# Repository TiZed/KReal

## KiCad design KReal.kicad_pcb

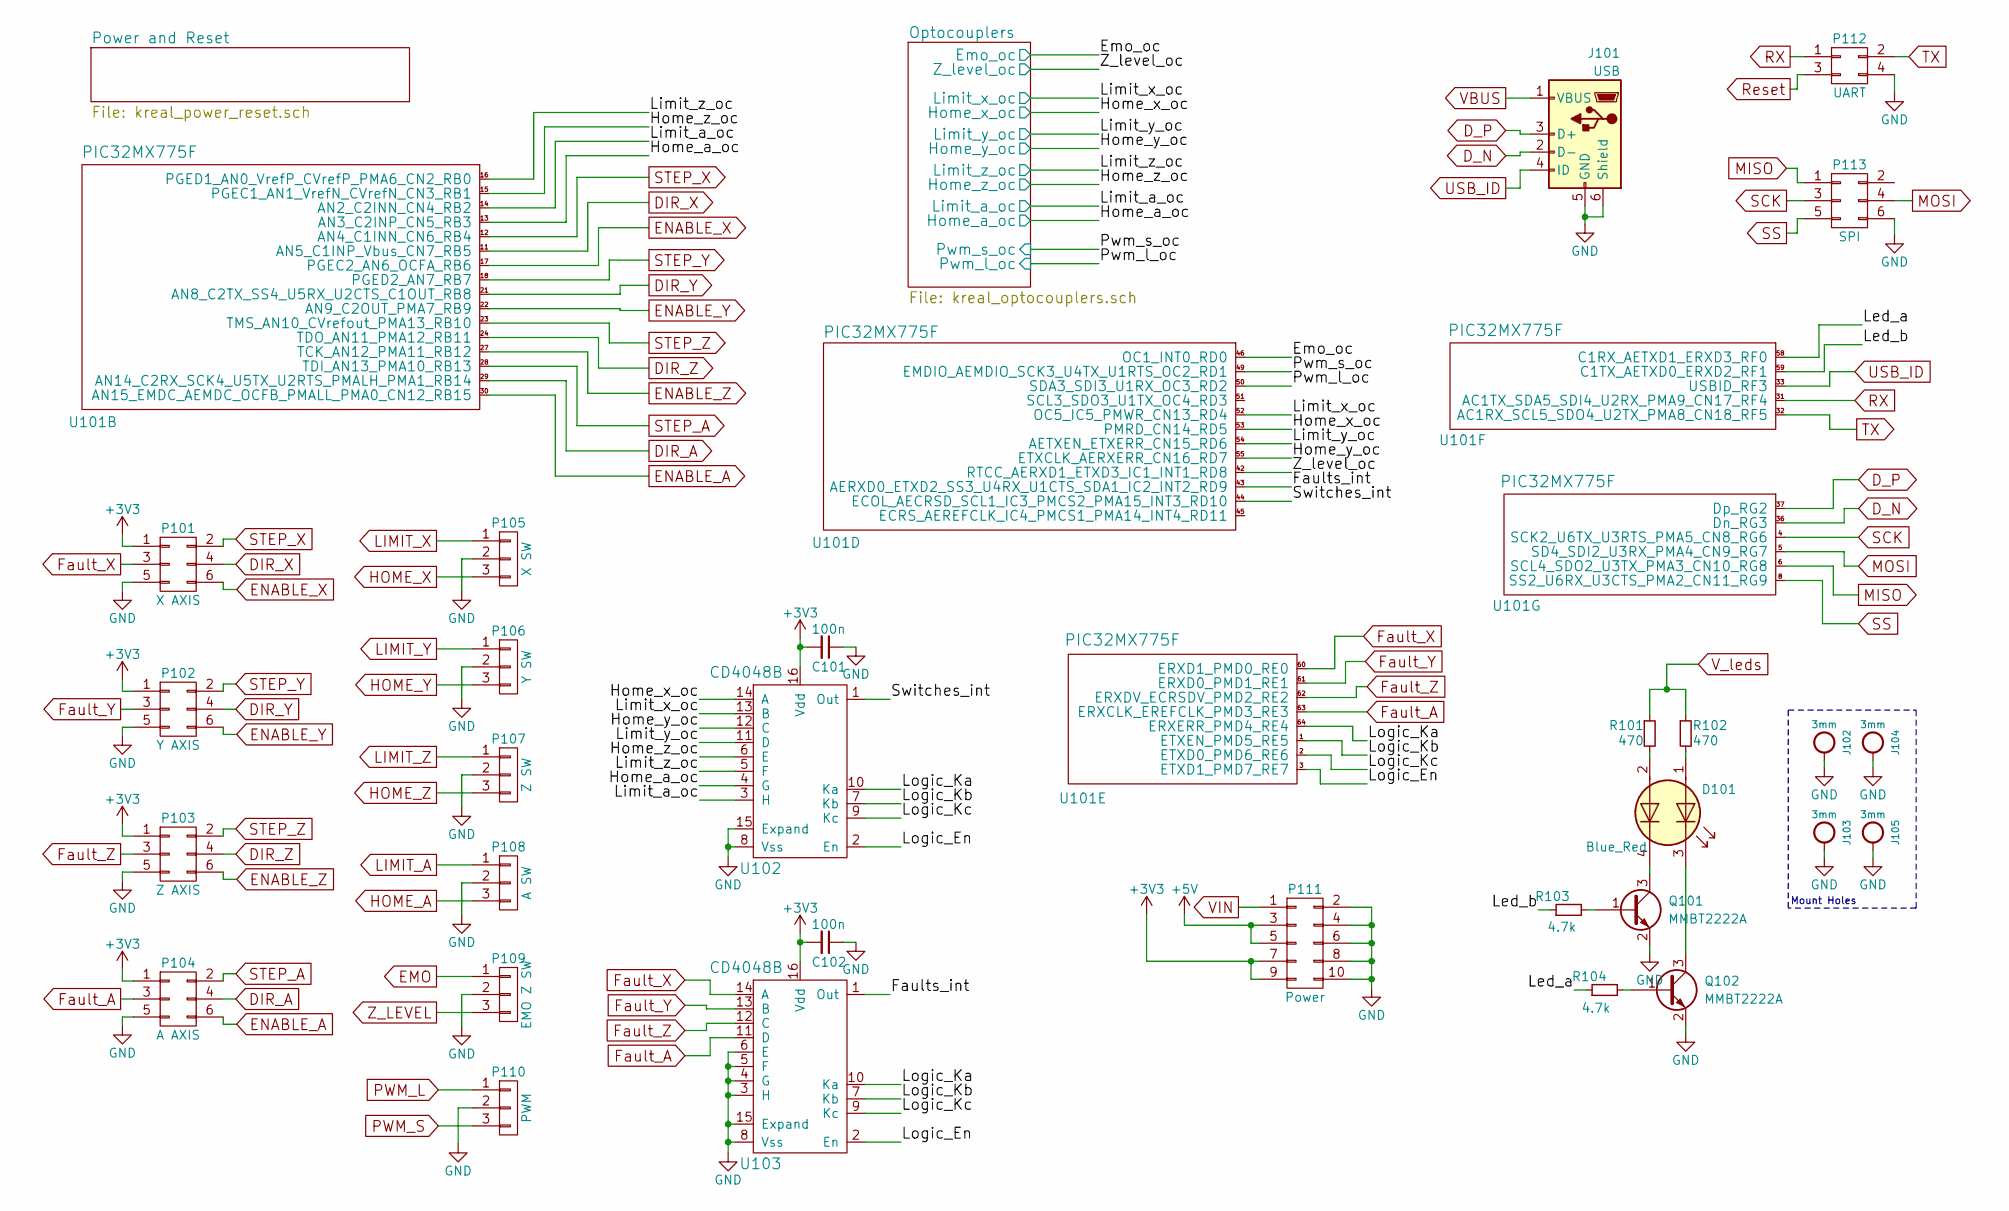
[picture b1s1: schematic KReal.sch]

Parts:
C101, C102: 100n; C_0603
D101: Blue_Red; LEDs_AACC_1.6mm_1.5mm
J101: USB; USB_Mini-B
J102, J103, J104, J105: 3mm; MountingHole_3mm_Pad
P101: X AXIS; Pin_Header_Straight_2x03_Pitch2.54mm
P102: Y AXIS; Pin_Header_Straight_2x03_Pitch2.54mm
P103: Z AXIS; Pin_Header_Straight_2x03_Pitch2.54mm
P104: A AXIS; Pin_Header_Straight_2x03_Pitch2.54mm
P105: X SW; Pin_Header_Straight_1x03_Pitch2.54mm
P106: Y SW; Pin_Header_Straight_1x03_Pitch2.54mm
P107: Z SW; Pin_Header_Straight_1x03_Pitch2.54mm
P108: A SW; Pin_Header_Straight_1x03_Pitch2.54mm
P109: EMO Z SW; Pin_Header_Straight_1x03_Pitch2.54mm
P110: PWM; Pin_Header_Straight_1x03_Pitch2.54mm
P111: Power; Pin_Header_Straight_2x05_Pitch2.54mm
P112: UART; Pin_Header_Straight_2x02_Pitch2.54mm
P113: SPI; Pin_Header_Straight_2x03_Pitch2.54mm
Q101, Q102: MMBT2222A; SOT-23
R101, R102: 470; R_0603
R103, R104: 4.7k; R_0603
U101: PIC32MX775F; TQFP-64_10x10mm_Pitch0.5mm
U102, U103: CD4048B; TSSOP-16_4.4x5mm_Pitch0.65mm

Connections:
+3V3: C101.2, C102.2, P101.1, P102.1, P103.1, P104.1, P111.7, P111.9, U102.16 (Vdd), U103.16 (Vdd); also elsewhere on the board
+5V: P111.3, P111.5; also elsewhere on the board
/Emo_oc: U101.46 (OC1_INT0_RD0); also elsewhere on the board
/Faults_int: U101.43 (AERXD0_ETXD2_SS3_U4RX_U1CTS_SDA1_IC2_IN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), U103.1 (Out)
/Home_a_oc: U101.13 (AN3_C2INP_CN5_RB3), U102.4 (G); also elsewhere on the board
/Home_x_oc: U101.53 (PMRD_CN14_RD5), U102.14 (A); also elsewhere on the board
/Home_y_oc: U101.55 (ETXCLK_AERXERR_CN16_RD7), U102.12 (C); also elsewhere on the board
/Home_z_oc: U101.15 (PGEC1_AN1_VrefN_CVrefN_CN3_RB1), U102.6 (E); also elsewhere on the board
/Led_a: R104.1, U101.58 (C1RX_AETXD1_ERXD3_RF0)
/Led_b: R103.1, U101.59 (C1TX_AETXD0_ERXD2_RF1)
/Limit_a_oc: U101.14 (AN2_C2INN_CN4_RB2), U102.3 (H); also elsewhere on the board
/Limit_x_oc: U101.52 (OC5_IC5_PMWR_CN13_RD4), U102.13 (B); also elsewhere on the board
/Limit_y_oc: U101.54 (AETXEN_ETXERR_CN15_RD6), U102.11 (D); also elsewhere on the board
/Limit_z_oc: U101.16 (PGED1_AN0_VrefP_CVrefP_PMA6_CN2_RB0), U102.5 (F); also elsewhere on the board
/Logic_En: U101.3 (ETXD1_PMD7_RE7), U102.2 (En), U103.2 (En)
/Logic_Ka: U101.64 (ERXERR_PMD4_RE4), U102.10 (Ka), U103.10 (Ka)
/Logic_Kb: U101.1 (ETXEN_PMD5_RE5), U102.7 (Kb), U103.7 (Kb)
/Logic_Kc: U101.2 (ETXD0_PMD6_RE6), U102.9 (Kc), U103.9 (Kc)
/Pwm_l_oc: U101.50 (SDA3_SDI3_U1RX_OC3_RD2); also elsewhere on the board
/Pwm_s_oc: U101.49 (EMDIO_AEMDIO_SCK3_U4TX_U1RTS_OC2_RD1); also elsewhere on the board
/Switches_int: U101.44 (ECOL_AECRSD_SCL1_IC3_PMCS2_PMA15_INT3_R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), U102.1 (Out)
/Z_level_oc: U101.42 (RTCC_AERXD1_ETXD3_IC1_INT1_RD8); also elsewhere on the board
DIR_A: P104.4, U101.29 (AN14_C2RX_SCK4_U5TX_U2RTS_PMALH_PMA1_RB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)
DIR_X: P101.4, U101.11 (AN5_C1INP_Vbus_CN7_RB5)
DIR_Y: P102.4, U101.21 (AN8_C2TX_SS4_U5RX_U2CTS_C1OUT_RB8)
DIR_Z: P103.4, U101.24 (TDO_AN11_PMA12_RB11)
D_N: J101.2 (D-), U101.36 (Dn_RG3)
D_P: J101.3 (D+), U101.37 (Dp_RG2)
EMO: P109.1; also elsewhere on the board
ENABLE_A: P104.6, U101.30 (AN15_EMDC_AEMDC_OCFB_PMALL_PMA0_CN12_RB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)
ENABLE_X: P101.6, U101.17 (PGEC2_AN6_OCFA_RB6); also elsewhere on the board
ENABLE_Y: P102.6, U101.22 (AN9_C2OUT_PMA7_RB9)
ENABLE_Z: P103.6, U101.27 (TCK_AN12_PMA11_RB12)
Fault_A: P104.3, U101.63 (ERXCLK_EREFCLK_PMD3_RE3), U103.11 (D)
Fault_X: P101.3, U101.60 (ERXD1_PMD0_RE0), U103.14 (A)
Fault_Y: P102.3, U101.61 (ERXD0_PMD1_RE1), U103.13 (B)
Fault_Z: P103.3, U101.62 (ERXDV_ECRSDV_PMD2_RE2), U103.12 (C)
GND: C101.1, C102.1, J101.5 (GND), J101.6 (Shield), J102.1, J103.1, J104.1, J105.1, P101.5, P102.5, P103.5, P104.5, P105.2, P106.2, P107.2, P108.2, P109.2, P110.2, P111.2, P111.4, P111.6, P111.8, P111.10, P112.4, P113.6, Q101.2 (E), Q102.2 (E), U102.8 (Vss), U102.15 (Expand), U103.3 (H), U103.4 (G), U103.5 (F), U103.6 (E), U103.8 (Vss), U103.15 (Expand); also elsewhere on the board
HOME_A: P108.3; also elsewhere on the board
HOME_X: P105.3; also elsewhere on the board
HOME_Y: P106.3; also elsewhere on the board
HOME_Z: P107.3; also elsewhere on the board
LIMIT_A: P108.1; also elsewhere on the board
LIMIT_X: P105.1; also elsewhere on the board
LIMIT_Y: P106.1; also elsewhere on the board
LIMIT_Z: P107.1; also elsewhere on the board
MISO: P113.1, U101.6 (SCL4_SDO2_U3TX_PMA3_CN10_RG8)
MOSI: P113.4, U101.5 (SD4_SDI2_U3RX_PMA4_CN9_RG7)
unnamed: D101.1 (A1), R102.2
unnamed: D101.2 (A2), R101.2
unnamed: D101.3 (K1), Q102.3 (C)
unnamed: D101.4 (K2), Q101.3 (C)
unnamed: Q101.1 (B), R103.2
unnamed: Q102.1 (B), R104.2
PWM_L: P110.1; also elsewhere on the board
PWM_S: P110.3; also elsewhere on the board
RX: P112.1, U101.31 (AC1TX_SDA5_SDI4_U2RX_PMA9_CN17_RF4)
Reset: P112.3; also elsewhere on the board
SCK: P113.3, U101.4 (SCK2_U6TX_U3RTS_PMA5_CN8_RG6)
SS: P113.5, U101.8 (SS2_U6RX_U3CTS_PMA2_CN11_RG9)
STEP_A: P104.2, U101.28 (TDI_AN13_PMA10_RB13)
STEP_X: P101.2, U101.12 (AN4_C1INN_CN6_RB4)
STEP_Y: P102.2, U101.18 (PGED2_AN7_RB7); also elsewhere on the board
STEP_Z: P103.2, U101.23 (TMS_AN10_CVrefout_PMA13_RB10)
TX: P112.2, U101.32 (AC1RX_SCL5_SDO4_U2TX_PMA8_CN18_RF5)
USB_ID: J101.4 (ID), U101.33 (USBID_RF3)
VBUS: J101.1 (VBUS); also elsewhere on the board
VIN: P111.1; also elsewhere on the board
V_leds: R101.1, R102.1; also elsewhere on the board
Z_LEVEL: P109.3; also elsewhere on the board

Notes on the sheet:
Mount Holes

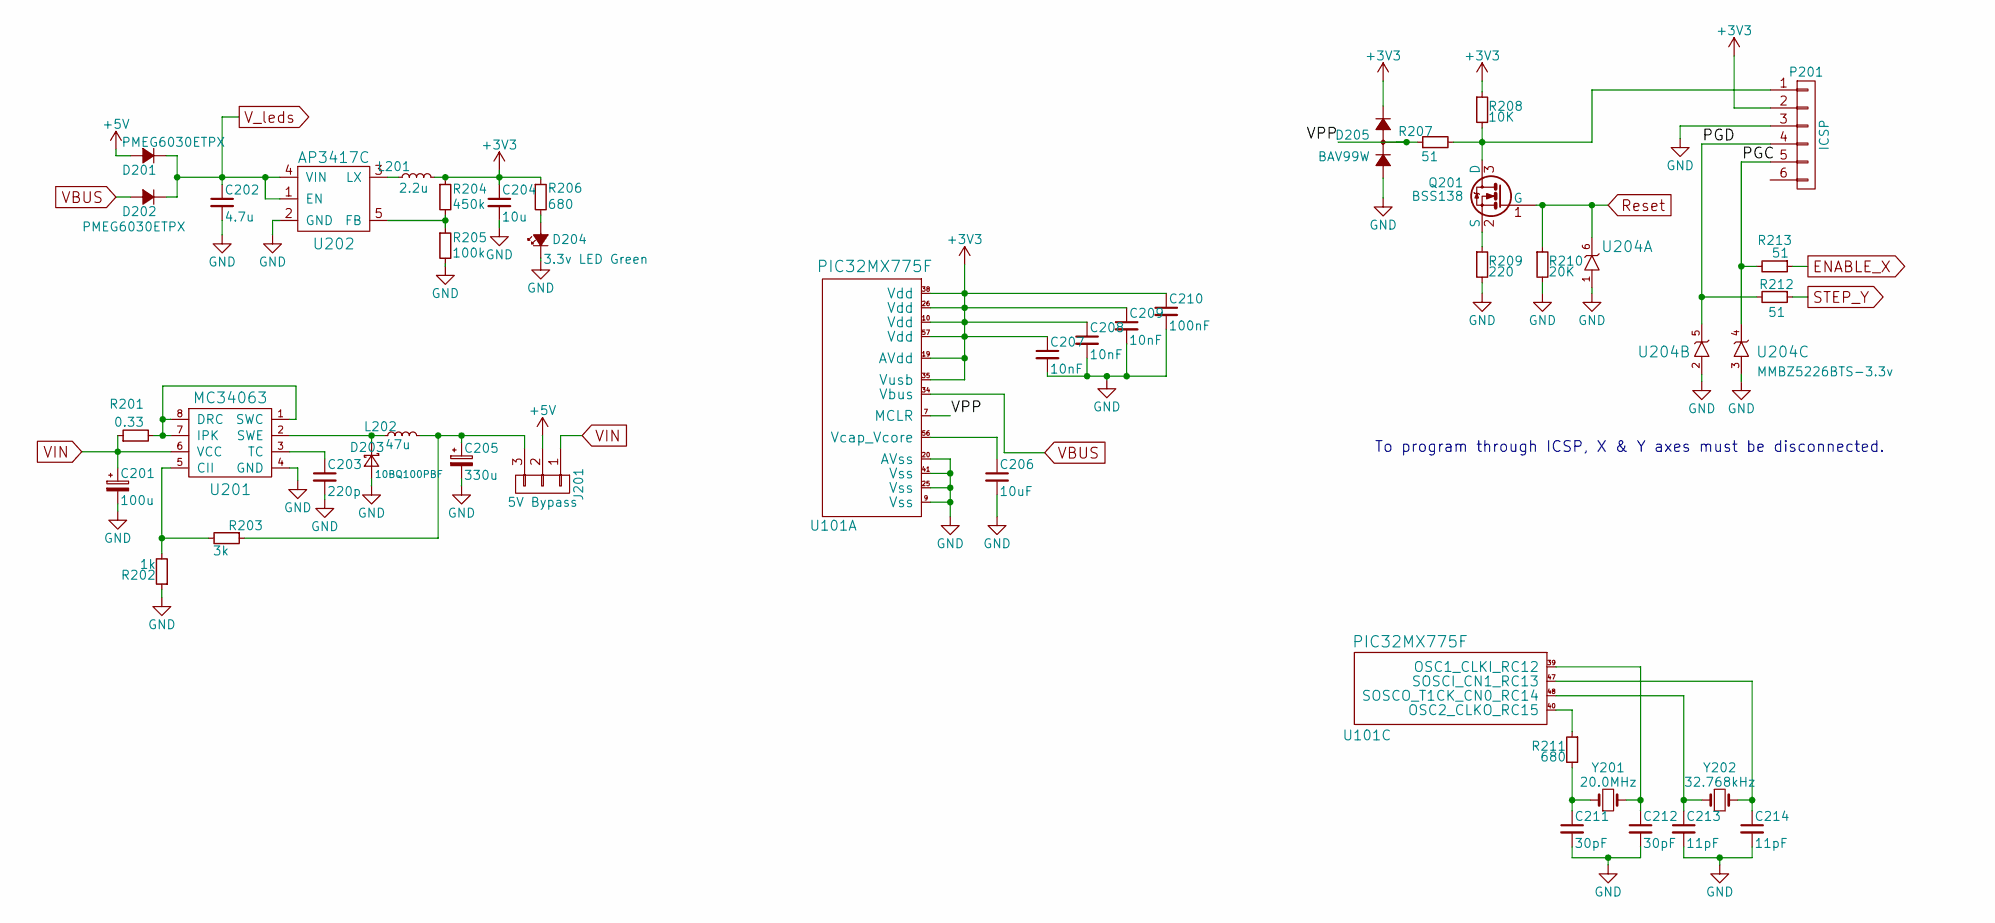
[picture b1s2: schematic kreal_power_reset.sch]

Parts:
C201: 100u; CP_Elec_6.3x7.7
C202: 4.7u; C_0603
C203: 220p; C_0603
C204: 10u; C_0603
C205: 330u; CP_Elec_8x10
C206: 10uF; C_0603
C207, C208, C209: 10nF; C_0603
C210: 100nF; C_0603
C211, C212: 30pF; C_0603
C213, C214: 11pF; C_0603
D201, D202: PMEG6030ETPX; D_SMA_Standard
D203: 10BQ100PBF; D_SMB_Standard
D204: 3.3v LED Green; LED_0603
D205: BAV99W; SOT-323_SC-70
J201: 5V Bypass; Pin_Header_Straight_1x03_Pitch2.54mm
L201: 2.2u; C_0805
L202: 47u; Inductor_Taiyo-Yuden_MD-5050
P201: ICSP; Pin_Header_Straight_1x06_Pitch2.54mm
Q201: BSS138; SOT-23
R201: 0.33; R_0805
R202: 1k; R_0603
R203: 3k; R_0603
R204: 450k; R_0603
R205: 100k; R_0603
R206, R211: 680; R_0603
R207, R212, R213: 51; R_0603
R208: 10K; R_0603
R209: 220; R_0603
R210: 20K; R_0603
U101: PIC32MX775F; TQFP-64_10x10mm_Pitch0.5mm
U201: MC34063; SOIC-8_3.9x4.9mm_Pitch1.27mm
U202: AP3417C; SOT-23-5
U204: MMBZ5226BTS-3.3v; SOT-363_SC-70-6
Y201: 20.0MHz; Crystal_SMD_0603-2pin_6.0x3.5mm
Y202: 32.768kHz; Crystal_SMD_MicroCrystal_CC5V-T1A-2pin_4.1x1.5mm

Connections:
+3V3: C204.1, C207.1, C208.1, C209.1, C210.1, D205.2 (A), L201.2, P201.2, R204.1, R206.1, R208.1, U101.10 (Vdd), U101.19 (AVdd), U101.26 (Vdd), U101.35 (Vusb), U101.38 (Vdd), U101.57 (Vdd); also elsewhere on the board
+5V: D201.2 (A), J201.2; also elsewhere on the board
/Power and Reset/PGC: P201.5, R213.2, U204.4
/Power and Reset/PGD: P201.4, R212.2, U204.5
/Power and Reset/VPP: D205.3 (AK), R207.1, U101.7 (MCLR)
ENABLE_X: R213.1; also elsewhere on the board
GND: C201.2, C202.2, C203.2, C204.2, C205.2, C206.2, C207.2, C208.2, C209.2, C210.2, C211.2, C212.2, C213.2, C214.2, D203.2 (A), D204.1 (K), D205.1 (K), P201.3, R202.1, R205.2, R209.2, R210.2, U101.9 (Vss), U101.20 (AVss), U101.25 (Vss), U101.41 (Vss), U201.4 (GND), U202.2 (GND), U204.1, U204.2, U204.3; also elsewhere on the board
unnamed: C203.1, U201.3 (TC)
unnamed: C205.1, J201.3, L202.2, R203.1
unnamed: C206.1, U101.56 (Vcap_Vcore)
unnamed: C211.1, R211.2, Y201.1
unnamed: C212.1, U101.39 (OSC1_CLKI_RC12), Y201.2
unnamed: C213.1, U101.48 (SOSCO_T1CK_CN0_RC14), Y202.1
unnamed: C214.1, U101.47 (SOSCI_CN1_RC13), Y202.2
unnamed: D203.1 (K), L202.1, U201.2 (SWE)
unnamed: D204.2 (A), R206.2
unnamed: L201.1, U202.3 (LX)
unnamed: P201.1, Q201.3 (D), R207.2, R208.2
unnamed: Q201.2 (S), R209.1
unnamed: R201.2, U201.1 (SWC), U201.7 (IPK), U201.8 (DRC)
unnamed: R202.2, R203.2, U201.5 (CII)
unnamed: R204.2, R205.1, U202.5 (FB)
unnamed: R211.1, U101.40 (OSC2_CLKO_RC15)
Reset: Q201.1 (G), R210.1, U204.6; also elsewhere on the board
STEP_Y: R212.1; also elsewhere on the board
VBUS: D202.2 (A), U101.34 (Vbus); also elsewhere on the board
VIN: C201.1, J201.1, R201.1, U201.6 (VCC); also elsewhere on the board
V_leds: C202.1, D201.1 (K), D202.1 (K), U202.1 (EN), U202.4 (VIN); also elsewhere on the board

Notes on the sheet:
To program through ICSP, X & Y axes must be disconnected.

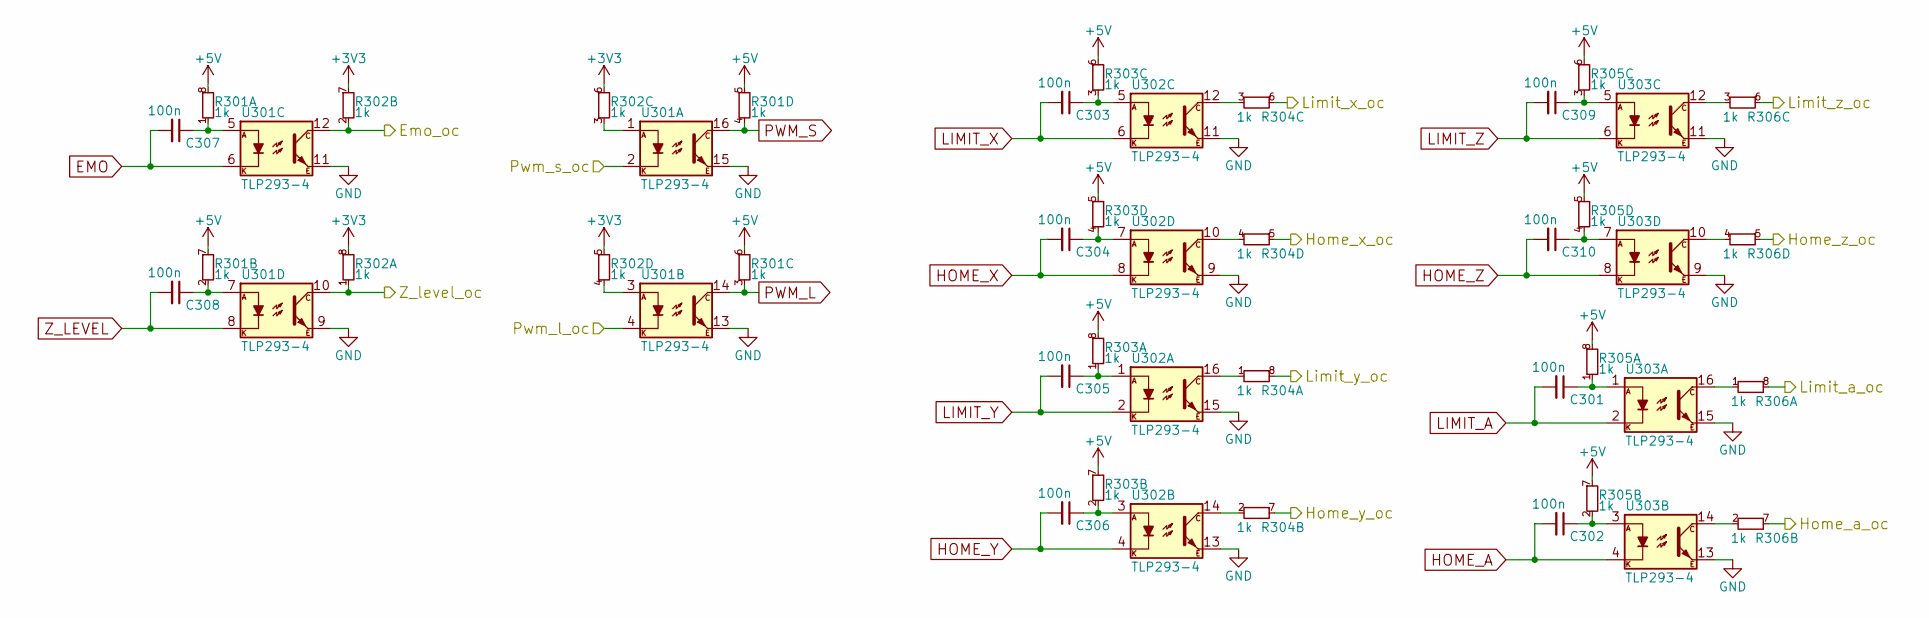
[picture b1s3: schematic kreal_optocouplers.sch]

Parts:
C301, C302, C303, C304, C305, C306, C307, C308, C309, C310: 100n; C_0603
R301, R302, R303, R304, R305, R306: 1k; R_Array_Concave_4x0603
U301, U302, U303: TLP293-4; SO-16-N

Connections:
+3V3: R302.5, R302.6, R302.7, R302.8; also elsewhere on the board
+5V: R301.5, R301.6, R301.7, R301.8, R303.5, R303.6, R303.7, R303.8, R305.5, R305.6, R305.7, R305.8; also elsewhere on the board
/Emo_oc: R302.2, U301.12; also elsewhere on the board
/Home_a_oc: R306.7; also elsewhere on the board
/Home_x_oc: R304.5; also elsewhere on the board
/Home_y_oc: R304.7; also elsewhere on the board
/Home_z_oc: R306.5; also elsewhere on the board
/Limit_a_oc: R306.8; also elsewhere on the board
/Limit_x_oc: R304.6; also elsewhere on the board
/Limit_y_oc: R304.8; also elsewhere on the board
/Limit_z_oc: R306.6; also elsewhere on the board
/Pwm_l_oc: U301.4; also elsewhere on the board
/Pwm_s_oc: U301.2; also elsewhere on the board
/Z_level_oc: R302.1, U301.10; also elsewhere on the board
EMO: C307.2, U301.6; also elsewhere on the board
GND: U301.9, U301.11, U301.13, U301.15, U302.9, U302.11, U302.13, U302.15, U303.9, U303.11, U303.13, U303.15; also elsewhere on the board
HOME_A: C302.2, U303.4; also elsewhere on the board
HOME_X: C304.2, U302.8; also elsewhere on the board
HOME_Y: C306.2, U302.4; also elsewhere on the board
HOME_Z: C310.2, U303.8; also elsewhere on the board
LIMIT_A: C301.2, U303.2; also elsewhere on the board
LIMIT_X: C303.2, U302.6; also elsewhere on the board
LIMIT_Y: C305.2, U302.2; also elsewhere on the board
LIMIT_Z: C309.2, U303.6; also elsewhere on the board
unnamed: C301.1, R305.1, U303.1
unnamed: C302.1, R305.2, U303.3
unnamed: C303.1, R303.3, U302.5
unnamed: C304.1, R303.4, U302.7
unnamed: C305.1, R303.1, U302.1
unnamed: C306.1, R303.2, U302.3
unnamed: C307.1, R301.1, U301.5
unnamed: C308.1, R301.2, U301.7
unnamed: C309.1, R305.3, U303.5
unnamed: C310.1, R305.4, U303.7
unnamed: R302.3, U301.1
unnamed: R302.4, U301.3
unnamed: R304.1, U302.16
unnamed: R304.2, U302.14
unnamed: R304.3, U302.12
unnamed: R304.4, U302.10
unnamed: R306.1, U303.16
unnamed: R306.2, U303.14
unnamed: R306.3, U303.12
unnamed: R306.4, U303.10
PWM_L: R301.3, U301.14; also elsewhere on the board
PWM_S: R301.4, U301.16; also elsewhere on the board
Z_LEVEL: C308.2, U301.8; also elsewhere on the board

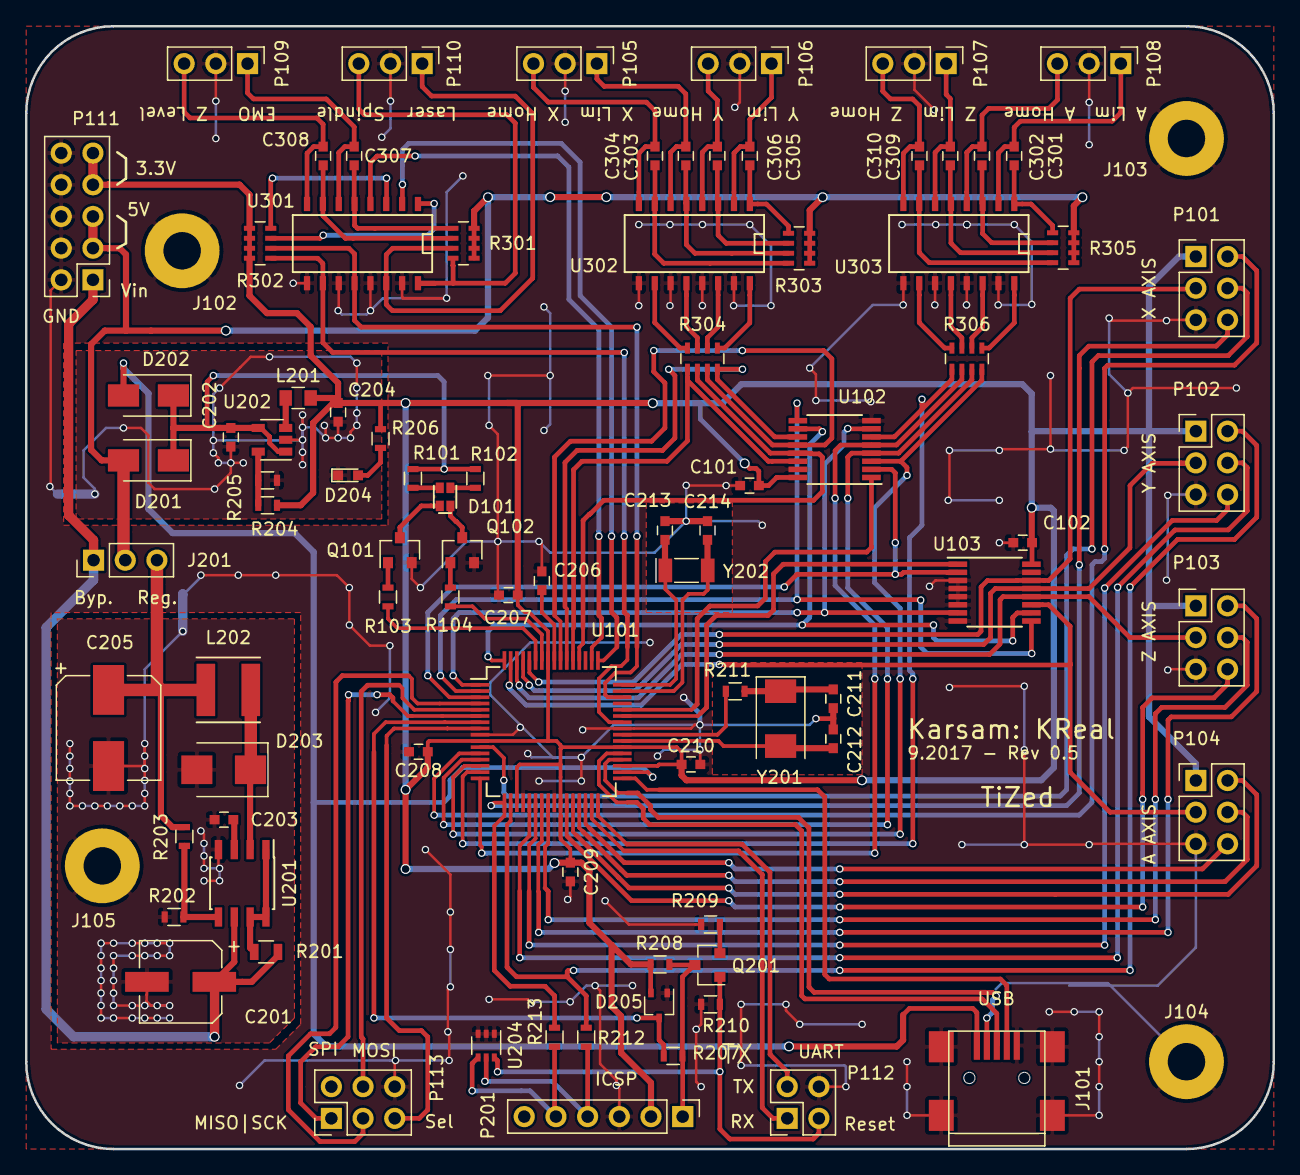
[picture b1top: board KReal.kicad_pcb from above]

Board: 2 copper layers, 100.0 x 90.0 mm, 91 parts (0 on the bottom side), 109 nets.

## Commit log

2017-05-26 First commit: PCB done, FW to follow
2017-06-20 Added schematic PDF
2017-07-05 First commit of chipKit Uno32 code.
2017-07-08 Adding SPI DMA transfer
2017-07-31 Continue SPI DMA code
2017-09-15 Fixed swapped USB N and P lanes in schematic. NOT fixed in layout yet.
2017-09-15 Fixed USB in layout. Fixed LEDs power source.
2017-09-20 Added CD4048B IC control. Changing switches and interrupts.
2017-09-21 Added external interrupts. Optimized SPI protocol.
2017-09-23 Added axis 'fault' signal setup. Added LEDs contorl
2017-09-23 Ignoring MPLABXLog files for GIT
2017-09-25 Fixed interrupts clearing. Activated secondary oscillator.
2017-09-30 Added LEDs blink. Some fixes to DMA and SPI configurations.
2017-10-06 Errata WA. Some minor optimization
2017-10-07 Finally got the DMA <-> SPI to work.
2017-10-08 Fixed interrupt edges. Some cleanup
2017-10-10 Logic fix for Logic IC.
2017-11-01 Fixed SPI padding and offsets bug
2017-11-15 Bytes swap done by DMA. Velocity command is now 64bits
2017-11-18 Some fixes due to HAL changes
2017-11-20 Fixed missing enabled check in stepgen
2017-11-25 Inverted axes, added invert option
2017-11-26 Some fixed to PWM
2017-11-27 Fixed tx checksum offset. Improved PWM rx loop.
2017-12-02 Fixed PWM frequency
2017-12-07 Fixed Z-Probe stuck on '1'
2017-12-11 Removed switches interrupt, now works by polling
2018-01-20 Fixed Z-Probe latchup and xsum race condition
